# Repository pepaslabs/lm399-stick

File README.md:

# lm399-stick

LM399, on a stick!!!

Latest release: [v1.3](kicad/releases/v1.3)

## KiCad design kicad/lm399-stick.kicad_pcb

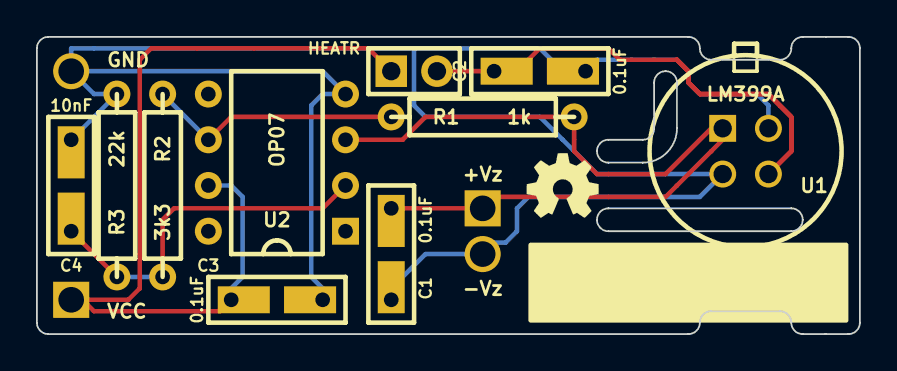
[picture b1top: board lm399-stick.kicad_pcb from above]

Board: 4 copper layers, 45.7 x 16.5 mm, 14 parts (0 on the bottom side), 6 nets.

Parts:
C1, C2, C3: 0.1uF; ANYSSCAP_SMALL_2_059B_0805
C4: 10nF; ANYSSCAP_SMALL_2_059B_0805
P1, P2, P3, P4: CONN_1X1; 1pin_056_079
P5: CONN_2X1; SIL-2
R1: 1k; R_AXIAL_0W25_059A_PL
R2: 3k3; R_AXIAL_0W25_059A_PL
R3: 22k; R_AXIAL_0W25_059A_PL
U1: LM399A; TO-46-PLASTIC
U2: OP07; DIP8_059A_PL

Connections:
+Vz: C1.1, P3.1, R1.2, U1.1, U2.3
-Vz: C1.2, C2.2, C3.2, C4.2, P2.1, P4.1, R3.2, U1.2, U1.4, U2.4
unnamed: C2.1, P5.2, U1.3
unnamed: C4.1, R2.2, R3.1, U2.2
unnamed: R1.1, R2.1, U2.6
Vcc: C3.1, P1.1, P5.1, U2.7

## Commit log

2017-05-21 Initial release
2017-05-21 adding schematic
2017-05-23 correcting Vz / Iz relationship (thanks carl_lab)
2018-03-28 old WIP
2018-03-28 updating parts
2018-03-28 project rename
2018-03-28 board shots
2018-03-28 correcting cap values
2018-03-28 updated schematic png
2018-03-28 why didnt this file update?
2018-04-28 v1.1
2018-04-29 using machine pin header footprints
2018-04-29 adding board shots
2018-04-29 readme
2022-08-05 updating lm399.py to use python3, adding diff.sh script
2022-08-07 v1.2
2022-08-21 todo
2022-08-26 v1.3
